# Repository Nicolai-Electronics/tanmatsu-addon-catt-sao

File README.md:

# Tanmatsu add-on: CATT to SAO

This repository contains the hardware design files for the CATT to SAO adapter.

## Documentation

Need the schematic? [It's in this repository as a PDF file](schematic.pdf).

## License

This hardware design may be used under the terms of the [CERN-OHL-P](LICENSE) license.

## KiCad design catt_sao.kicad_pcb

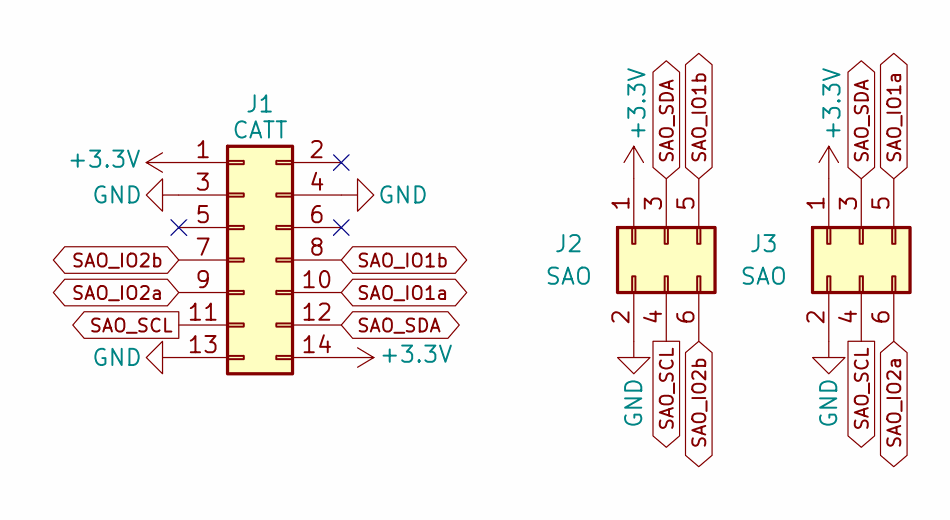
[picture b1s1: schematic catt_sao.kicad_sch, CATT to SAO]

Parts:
J1: CATT; PinHeader_2x07_P2.54mm_Horizontal; LCSC C19190502
J2, J3: SAO; PinSocket_2x03_P2.54mm_Vertical

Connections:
+3.3V: J1.1, J1.14, J2.1, J3.1
GND: J1.3, J1.4, J1.13, J2.2, J3.2
SAO_IO1a: J1.10, J3.5
SAO_IO1b: J1.8, J2.5
SAO_IO2a: J1.9, J3.6
SAO_IO2b: J1.7, J2.6
SAO_SCL: J1.11, J2.4, J3.4
SAO_SDA: J1.12, J2.3, J3.3

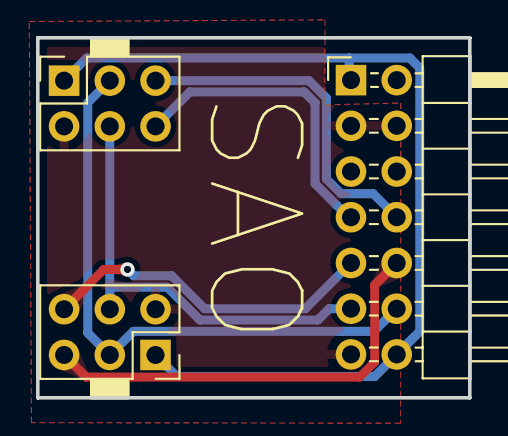
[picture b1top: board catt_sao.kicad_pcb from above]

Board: 2 copper layers, 24.0 x 20.0 mm, 3 parts (0 on the bottom side), 8 nets.

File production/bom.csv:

Designator,Footprint,Quantity,Value,LCSC Part #
J1,PinHeader_2x07_P2.54mm_Horizontal,1,CATT,C19190502
"J2, J3",PinSocket_2x03_P2.54mm_Vertical,2,SAO,

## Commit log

2025-05-13 Version 2

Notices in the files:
catt_sao.kicad_sch:
License: CERN-OHL-P
Copyright © 2025 Nicolai Electronics
